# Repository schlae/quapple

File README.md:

# Quapple - A Quadlink Clone
What is a Quadlink? It's an ISA expansion card from the '80s designed to turn your IBM PC (such as a 5150 or 5160) into an Apple \]\[! After booting and running the software, you can switch quickly between PC and Apple mode using Ctrl-Alt-A (for Apple) and Ctrl-Alt-P (for PC).

I'm not selling this board, but the complete design files are available here so you can build it yourself. As an alternative, [a2heaven](http://www.a2heaven.com/webshop/index.php?rt=product/product&product_id=177) sells a kit with the PCB and all the components. (I have not personally built one of these kits.)

All of the components are readily available. In the bill of materials, Mouser part numbers are listed where available. The RAM chips, 27C32 ROM chip, and NE558 may be obtained from a variety of sources in China, but they are not guaranteed to work, so I recommend getting 1 or 2 extras just in case. Note: It has been reported that a Signetics NE558 with a date code of 8825VI, commonly available from China, does not actually work. If you can't find any working 558 chips, try building [my replacement that uses four 555 chips](https://oshpark.com/shared_projects/zHGURt7g).

[Schematic](https://github.com/schlae/quapple/blob/main/Quapple.pdf)

[Bill of Materials](https://github.com/schlae/quapple/blob/main/Quapple.csv)

Please note that the 0.1" header pins are *not* listed on the BOM. They are standard breakaway headers.

The memory chips (4416 and 4164 RAM) are both 150ns types.

[Fab Files](https://github.com/schlae/quapple/blob/main/fab/Quapple-rev1.zip)

## Fabrication Notes
This board is a straight forward 2-layer board. Ideally you should specify selective gold plating (hard gold) for the edge fingers, but this gets very expensive for small orders. ENIG will work but the gold will rub off fairly quickly.

Board dimensions are 13.335" x 4.24" (338.7mm x 107.7mm).

For the soldermask color, pick whatever you want!

## Assembly Notes
I recommend using sockets for the memory chips, CPU, and all the PALS. You'll also need a socket for the joystick/paddle connector. The list of sockets required is as follows:

| Quantity |  Position      | Type              |
|----------|----------------|-------------------|
| 9        | U1-U4, U20-U23, J4 | 16-pin, 0.3" wide |
| 2        | U5, U24        | 18-pin, 0.3" wide |
| 1        | U11            | 24-pin, 0.6" wide |
| 1        | U48            | 40-pin, 0.6" wide |
| 10       | U7, U8, U27, U30, U33, U34, U40, U49, U50, U51 | 20-pin, 0.3" wide |

If you plan to install the card in an IBM 5150 or 5160, you'll plug the floppy drive cable (the one going between the existing controller and the floppy drives in your computer) into the P2 edge connector on the card. **Solder a shrouded header at the J7 position with the keying notch pointing downwards.** Later on, you'll make a short cable to go between the floppy controller card and J7.

If you want to use the card in another system (note: I have not tested this yet!) with a standard IDC header instead of an edge card connector, **solder unshrouded headers at both the J7 and P3 position.** Your existing floppy cable will plug into P3, and you will need to make a short cable that connects J7 and your existing floppy controller card.

J5 and J6 are right-angle 0.1" headers. You can use a single 8-pin strip. Remember to pull pin 2 on both header positions since this is the key for the cable that plugs in. This is also marked on the back of the PC board.

If you are using an NMOS 6502, you can connect the solder jumper on the back of the board right next to the chip. CMOS 6502 chips repurpose this pin and the solder jumper should be left open.

Note for European users: it might be tempting to configure the solder jumpers on the back of the card for PAL timings rather than NTSC, but I have not tested this configuration. The original Quadlink has solder paste covering the jumpers, implying that they never fully tested it. Use it at your own risk.

## Bracket
I've created a CAD model of the original Quadlink bracket. If you have access to sheet metal tools (or even just a chassis nibbler) then you can reproduce it. Once it is in the right shape, bend the top using a press brake or even just a bench vise. The material is 0.035" (0.9mm) steel, brushed and painted black.

[CAD drawing of bracket](https://github.com/schlae/quapple/blob/main/mech/bracket.dxf)

## Programmable Devices
There are 11 programmable devices on the Quapple. One of them is a 27C32 EPROM which contains the character set for the text mode. I didn't have much luck using the Minipro TL866 device to program my Intel 2732 devices, so you might have to try a few to find one that works. You might also try using a flash device (28C32?) instead, but I have not tested this myself.

[EPROM binary](https://github.com/schlae/quapple/blob/main/eprom/U11QL100.bin)

The remaining programmable devices are all PALs. You can use an ATF16V8 (speed grade is unimportant here), which happens to be supported by the Minipro TL866.

[PAL files](https://github.com/schlae/quapple/tree/main/pals)

Use the JEDEC files (.jed) with the following Minipro command line under Linux:

`minipro -p "ATF16V8B" -w [file.jed] -P`

The full, commented, PAL source code is provided for educational purposes. If you want to modify them, you can use WinCUPL to build them.

I recommend marking the PALs with colored dots, labels, or permanent marker so you don't mix them up and put them in the wrong sockets.

PAL functions are as follows:

| Position   |   Function    |
|------------|---------------|
| U8         | Video address decoding (simple) |
| U27        | Video address decoding (complex). Video sync. |
| U7         | Clock generation |
| U30        | Soft switches |
| U33        | Color attribute generation |
| U34        | ISA bus address decoder |
| U40        | Disk controller |
| U49        | 6502 state machine |
| U50        | More soft switches |
| U51        | RAM/ROM mapping, CAS control, RESET inverter |

## Cable assemblies
You will also need to build several cable assemblies to connect the Quapple to your PC.

### Floppy drive cable
For use with an IBM 5150 or 5160, make a short, 6" (15cm) IDC ribbon cable, 34 pin, with a 0.1" female header at one end and a 34-pin female edge connector at the other end.

For any other computer, just crimp a 34-pin 0.1" female header at both ends. Be sure not to get pin 1 mixed up--it is very easy to do!

### Video loopback cable
To use the same monitor for both Apple and PC mode, you'll need a short cable to go between the Quapple and your regular video card (MDA or CGA). This is just a short cable with a male DE-9 connector at both ends, wired straight through (pin 1 to pin 1, etc).

The stock cable is 12" (30.5cm) long and uses a TE Connectivity/AMP 745032-1 connector, along with a cord guard, 207753-1, at both ends. The contact part number is 1-66506-0. The cable is 0.24" (6mm) diameter with eight conductors (the drain wire is connected to pin 1).

### PC speaker jumper
To hear Apple sound through the PC speaker, make a short 2-wire cable (maybe 2-3" long, depending on your computer). This goes from the motherboard to the Quapple.

The cable should be wired as follows:

* Pin 1 connects to pin 1 (black wire)
* Pin 2 is a key (plastic peg inserted in the opening) at both ends
* Pin 3 is not used
* Pin 4 to pin 4 (yellow wire)

## Installation
You'll want to install the card in the second-to-last slot (5150) or third-from-last slot (5160). This is because the floppy controller should be in between the Quapple and the power supply, just to make cable routing easier.

Before you start, plug the short floppy jumper cable into J7 on the Quapple. Also plug the 4-pin PC speaker jumper cable into header J6.

Remove the floppy controller and disconnect the drive cable from it. Plug the drive cable into the Quapple connector P2 (or P3, if the cable has a 0.1" socket at the end). Unplug the PC speaker from the motherboard.

Then plug the Quapple into the PC slot, managing the floppy cable as needed. The 4-pin jumper should plug into the motherboard's PC speaker header, and the PC speaker cable should plug into J5.

Then plug the short floppy jumper cable into the header on the floppy controller, and plug the floppy controller back into an adjacent slot. Since the card is shorter, it's much easier to use the slot that is closer to the power supply.

Finally, connect the DE-9 jumper cable between the video card and the *lower* connector on the Quapple. This step is optional since you can use the card with a dual monitor configuration, or even with the composite video output jack.

## Software
You can find the software at the link below, along with the manual of the original Quadlink. There are *three* disk images you will need: the Quadlink System Master, the Quadlink Filer, and DOS (I used PC DOS 1.10, but feel free to experiment). The Quadlink System Master disk has an executable, QUADLINK.EXE, which should be copied to the DOS disk.

The Filer disk can be written using a flux imaging tool, or possibly with an Apple II running ADTPro.

[Software download](https://www.diskman.com/presents/trackstar/software.htm)

A note about compatibility: I have only tested the card in an IBM 5150. It's supposed to work in a 5160 as well. Based on looking at the design, I see no reason why it wouldn't work in a faster machine, but there may be CPU-dependent hardware loops in the Quadlink executable that would prevent it from working.

Once you have the disks, insert the DOS disk and turn on the computer. After it boots, run QUADLINK.EXE and follow the prompts. When you insert the Filer disk, the software copies the entire Applesoft ROM from the disk into a special 16K memory on the card and write-protects it. Hit a key to get back to DOS, and then press CTRL-ALT-A. If you see the Quadlink banner, hit CTRL-ALT-DEL to boot the Apple.

## Troubleshooting
This can be a tricky card to troubleshoot. The QUADLINK.EXE doesn't really provide good error diagnostics, but if you can get it to access the Filer disk, then you know that the 6502 is running code and trying to copy data from the disk.

Someday, when I get a chance, I'll look into writing a diagnostic program to help with the process...

## License
This work is licensed under a Creative Commons Attribution-ShareAlike 4.0
International License. See [https://creativecommons.org/licenses/by-sa/4.0/](https://creativecommons.org/licenses/by-sa/4.0/).

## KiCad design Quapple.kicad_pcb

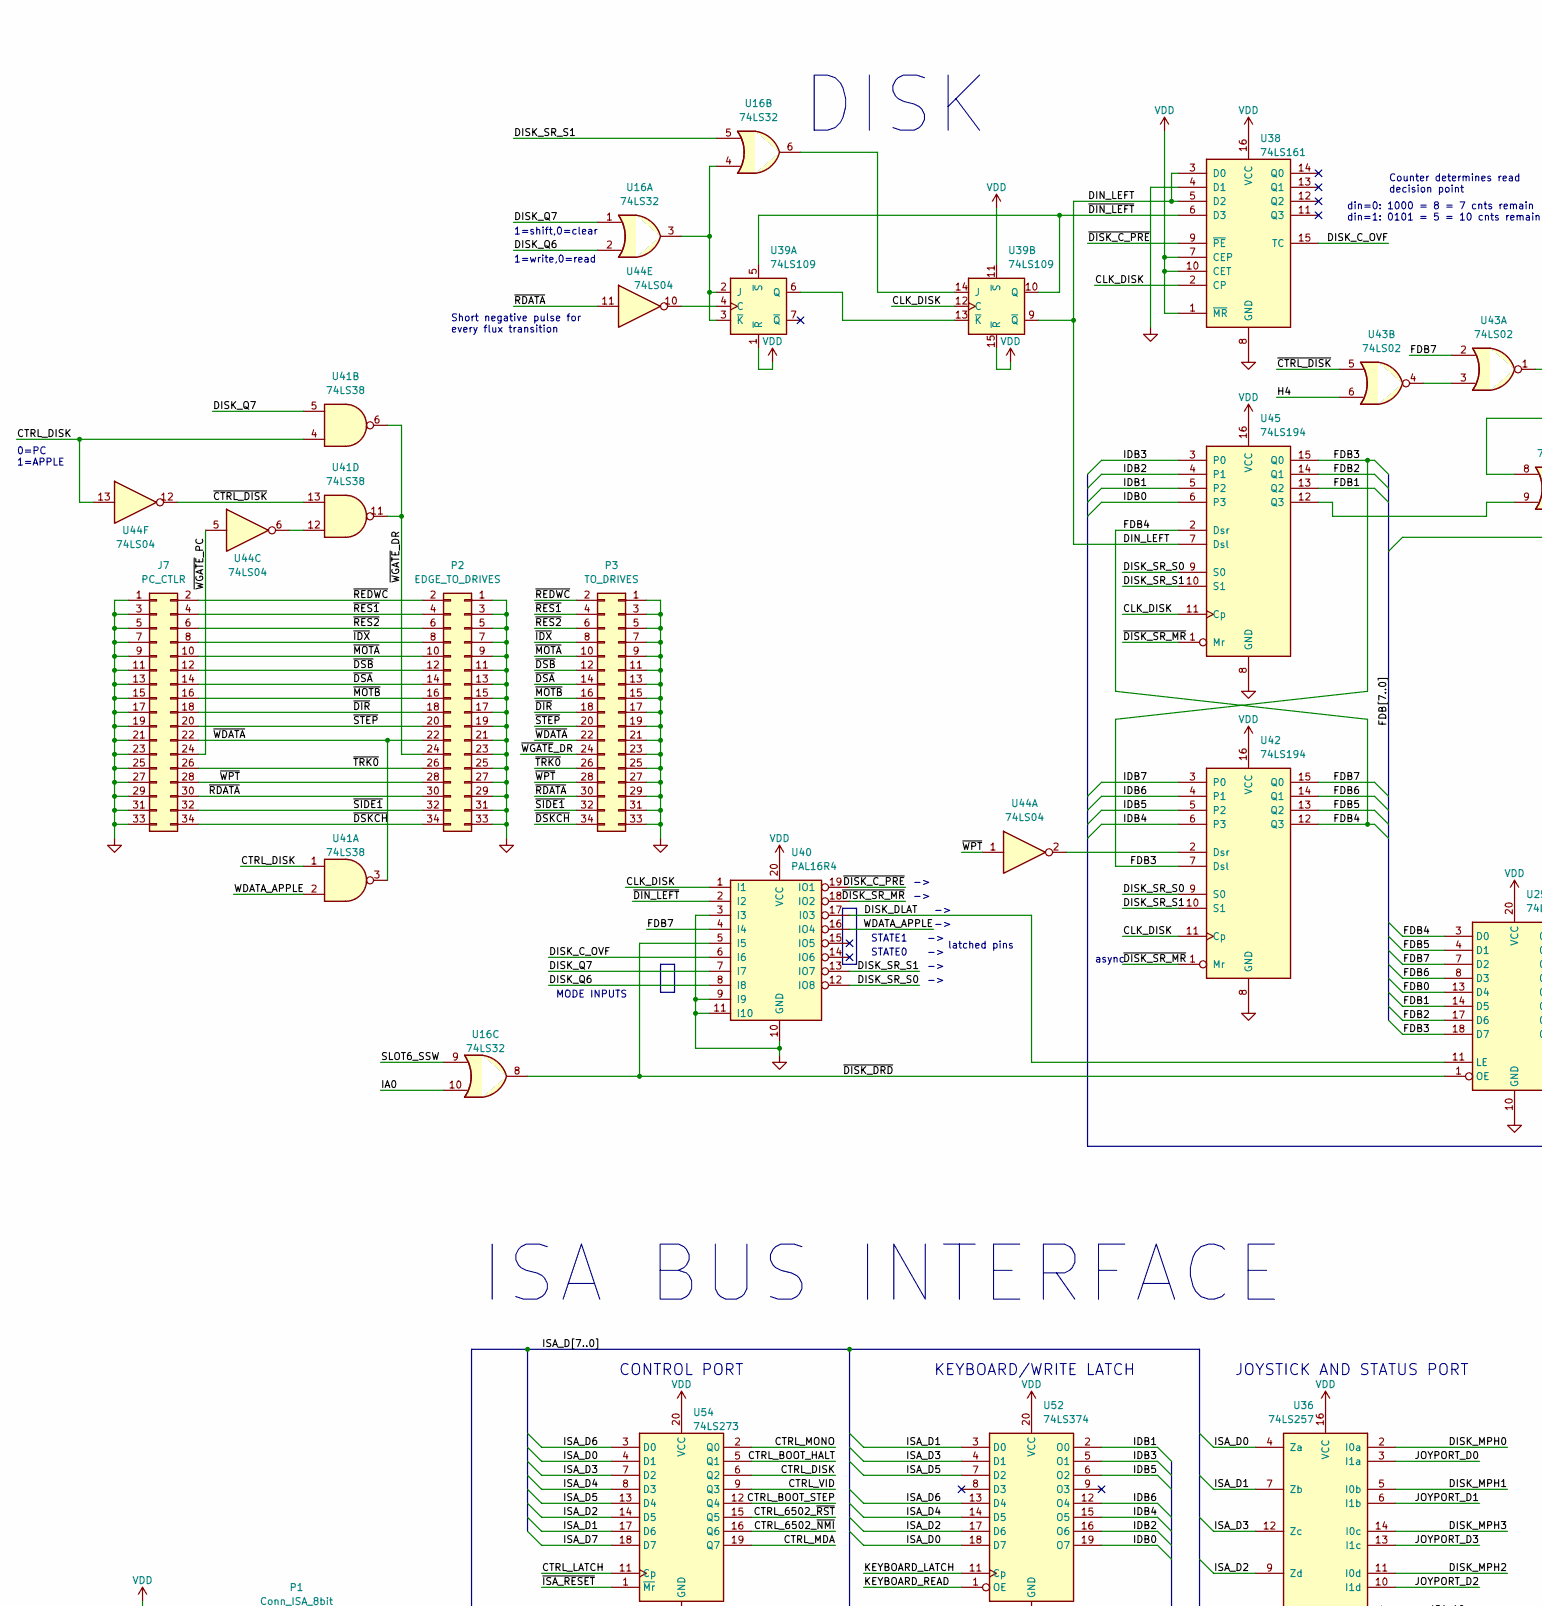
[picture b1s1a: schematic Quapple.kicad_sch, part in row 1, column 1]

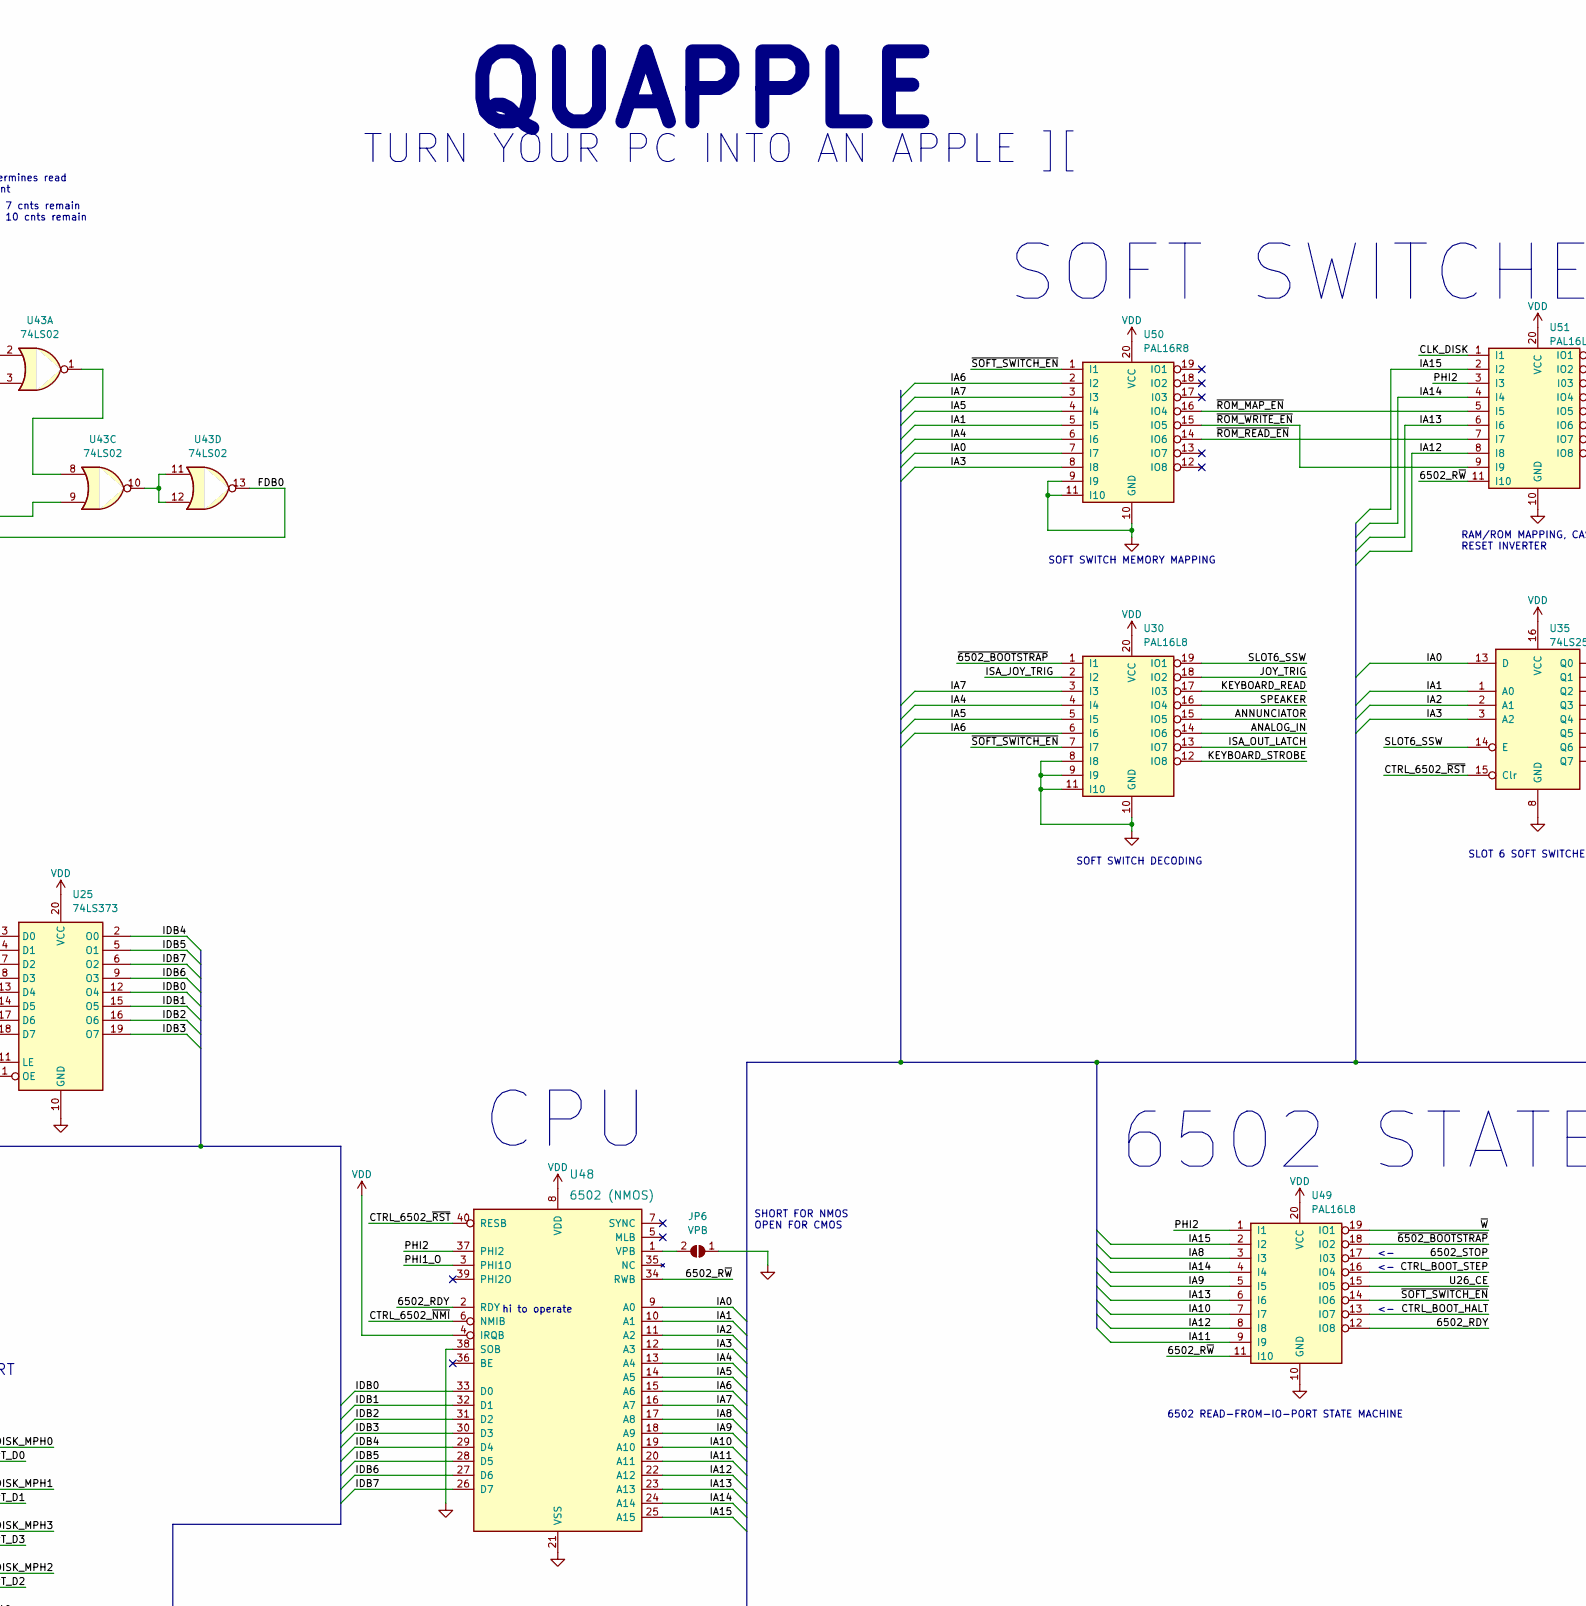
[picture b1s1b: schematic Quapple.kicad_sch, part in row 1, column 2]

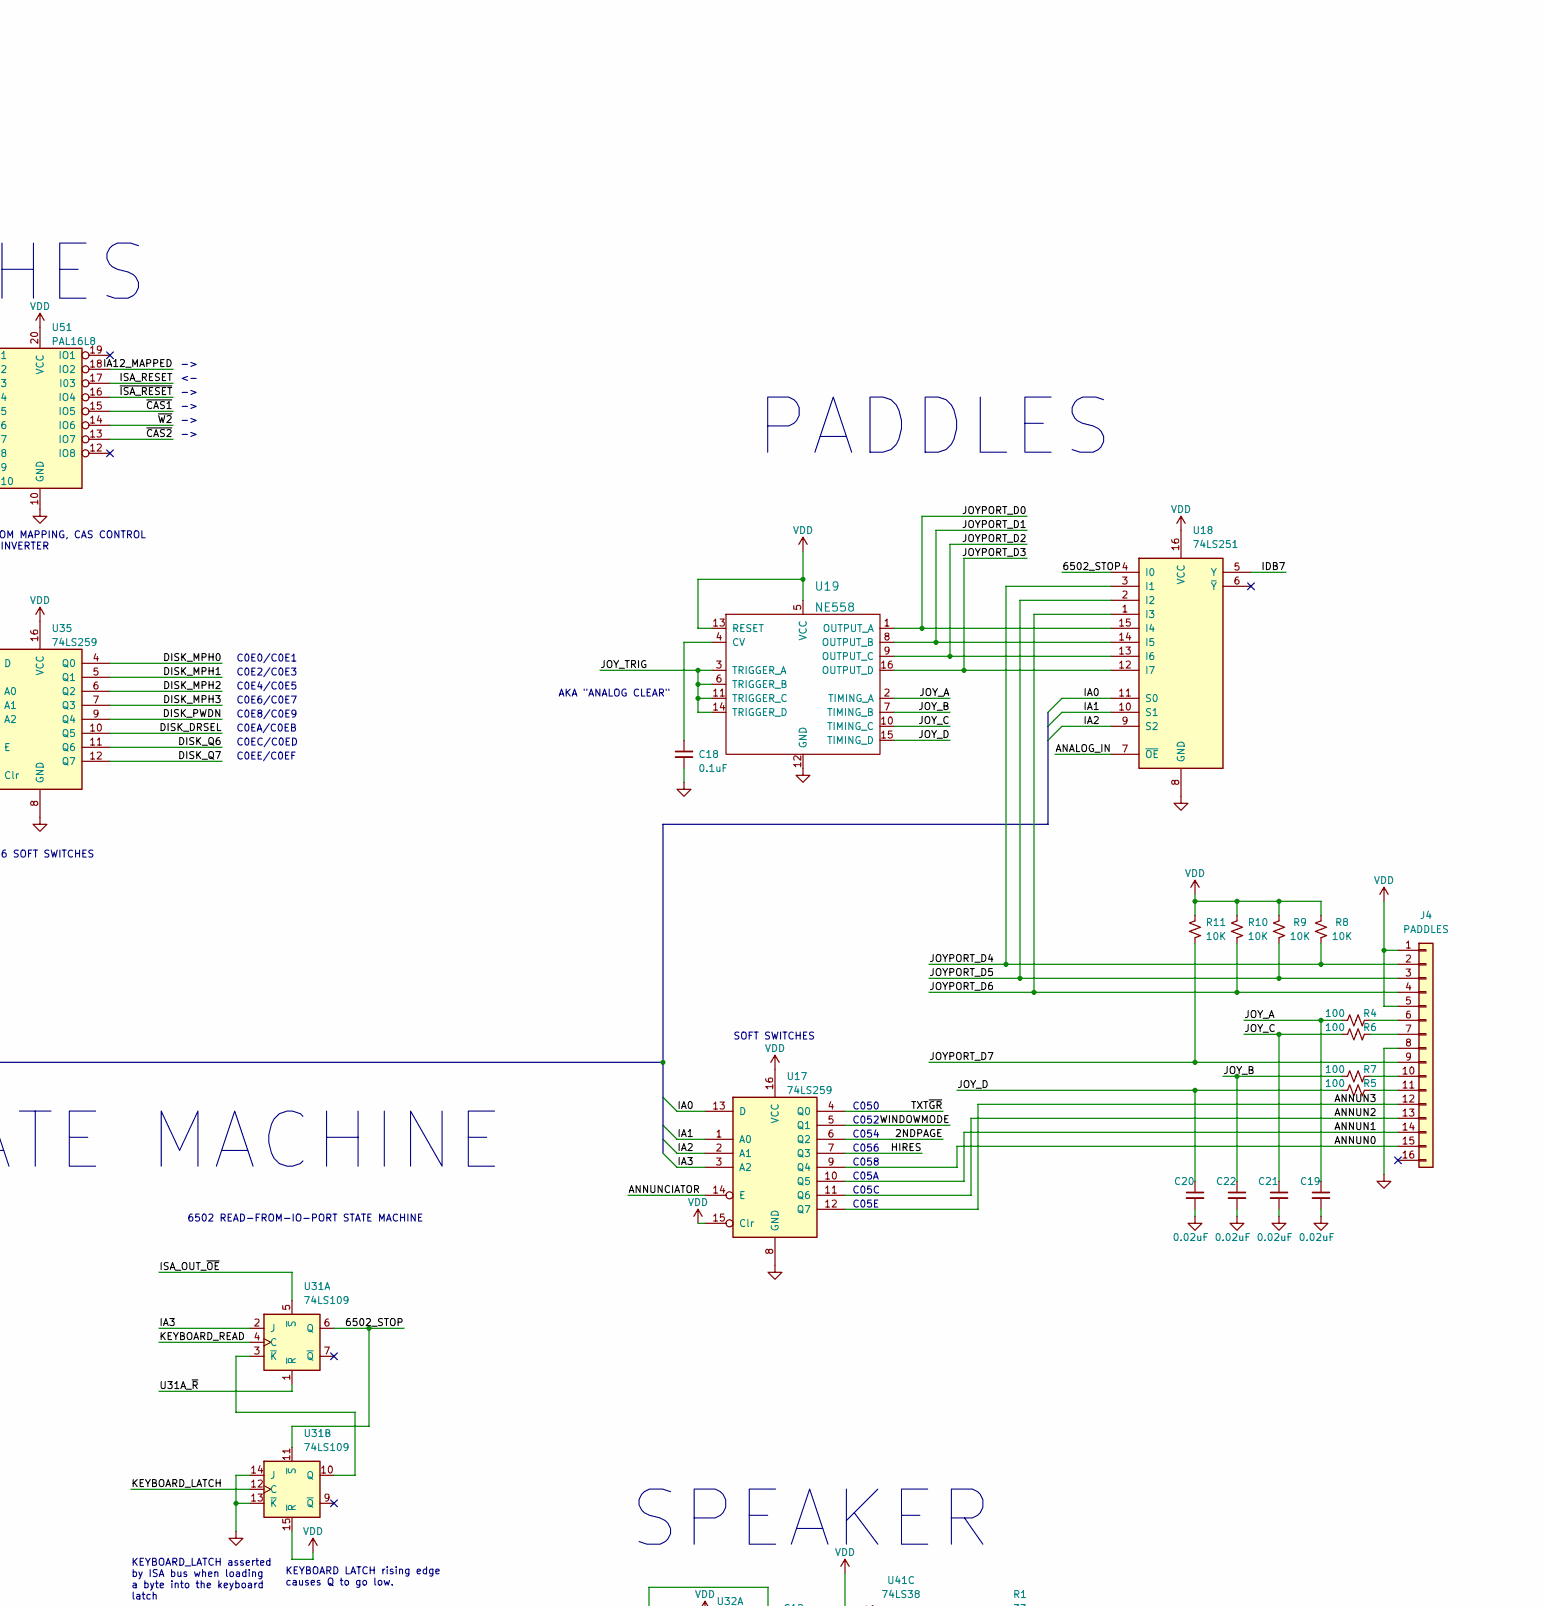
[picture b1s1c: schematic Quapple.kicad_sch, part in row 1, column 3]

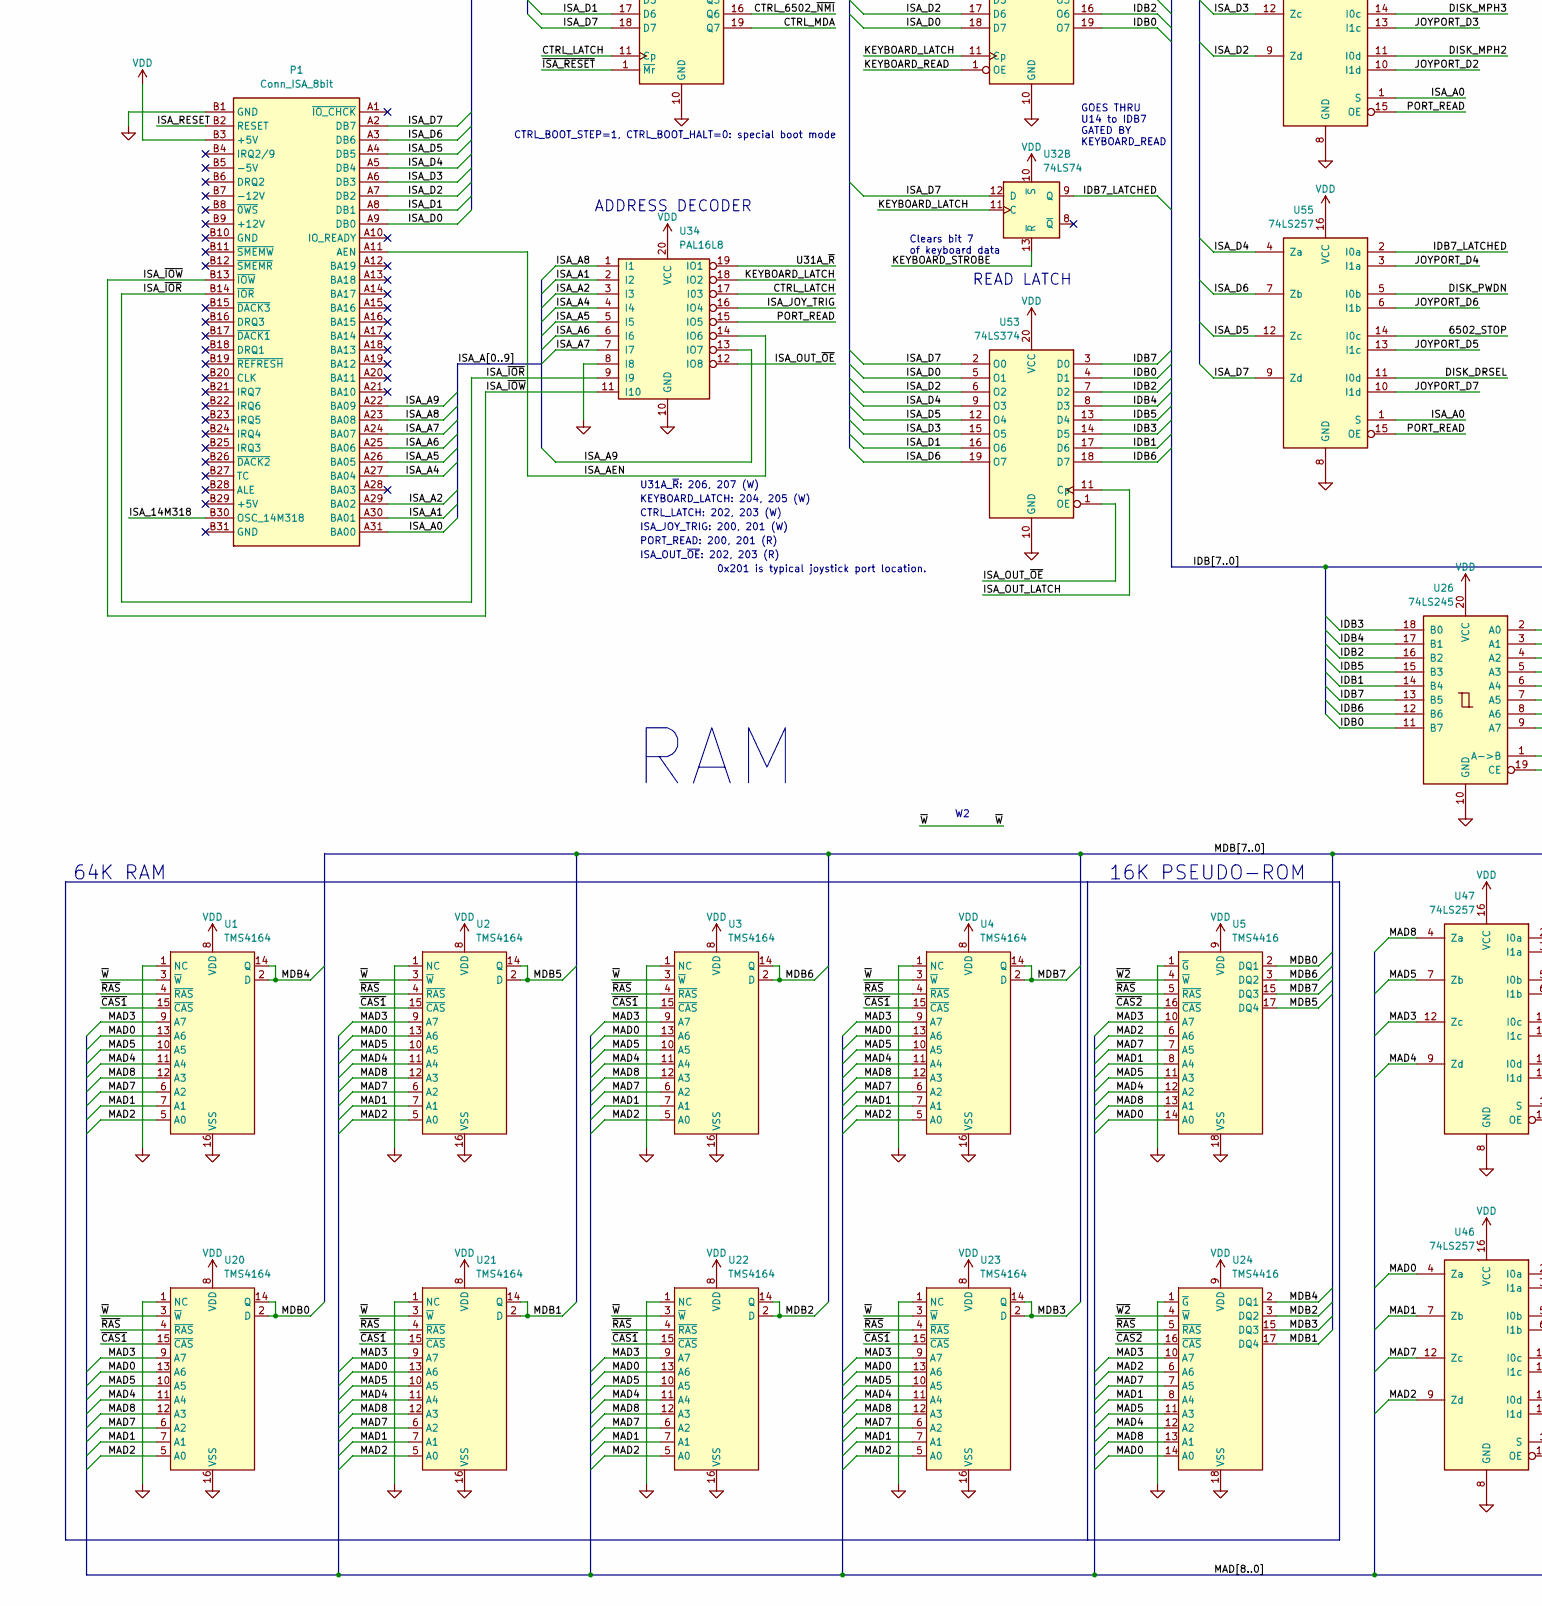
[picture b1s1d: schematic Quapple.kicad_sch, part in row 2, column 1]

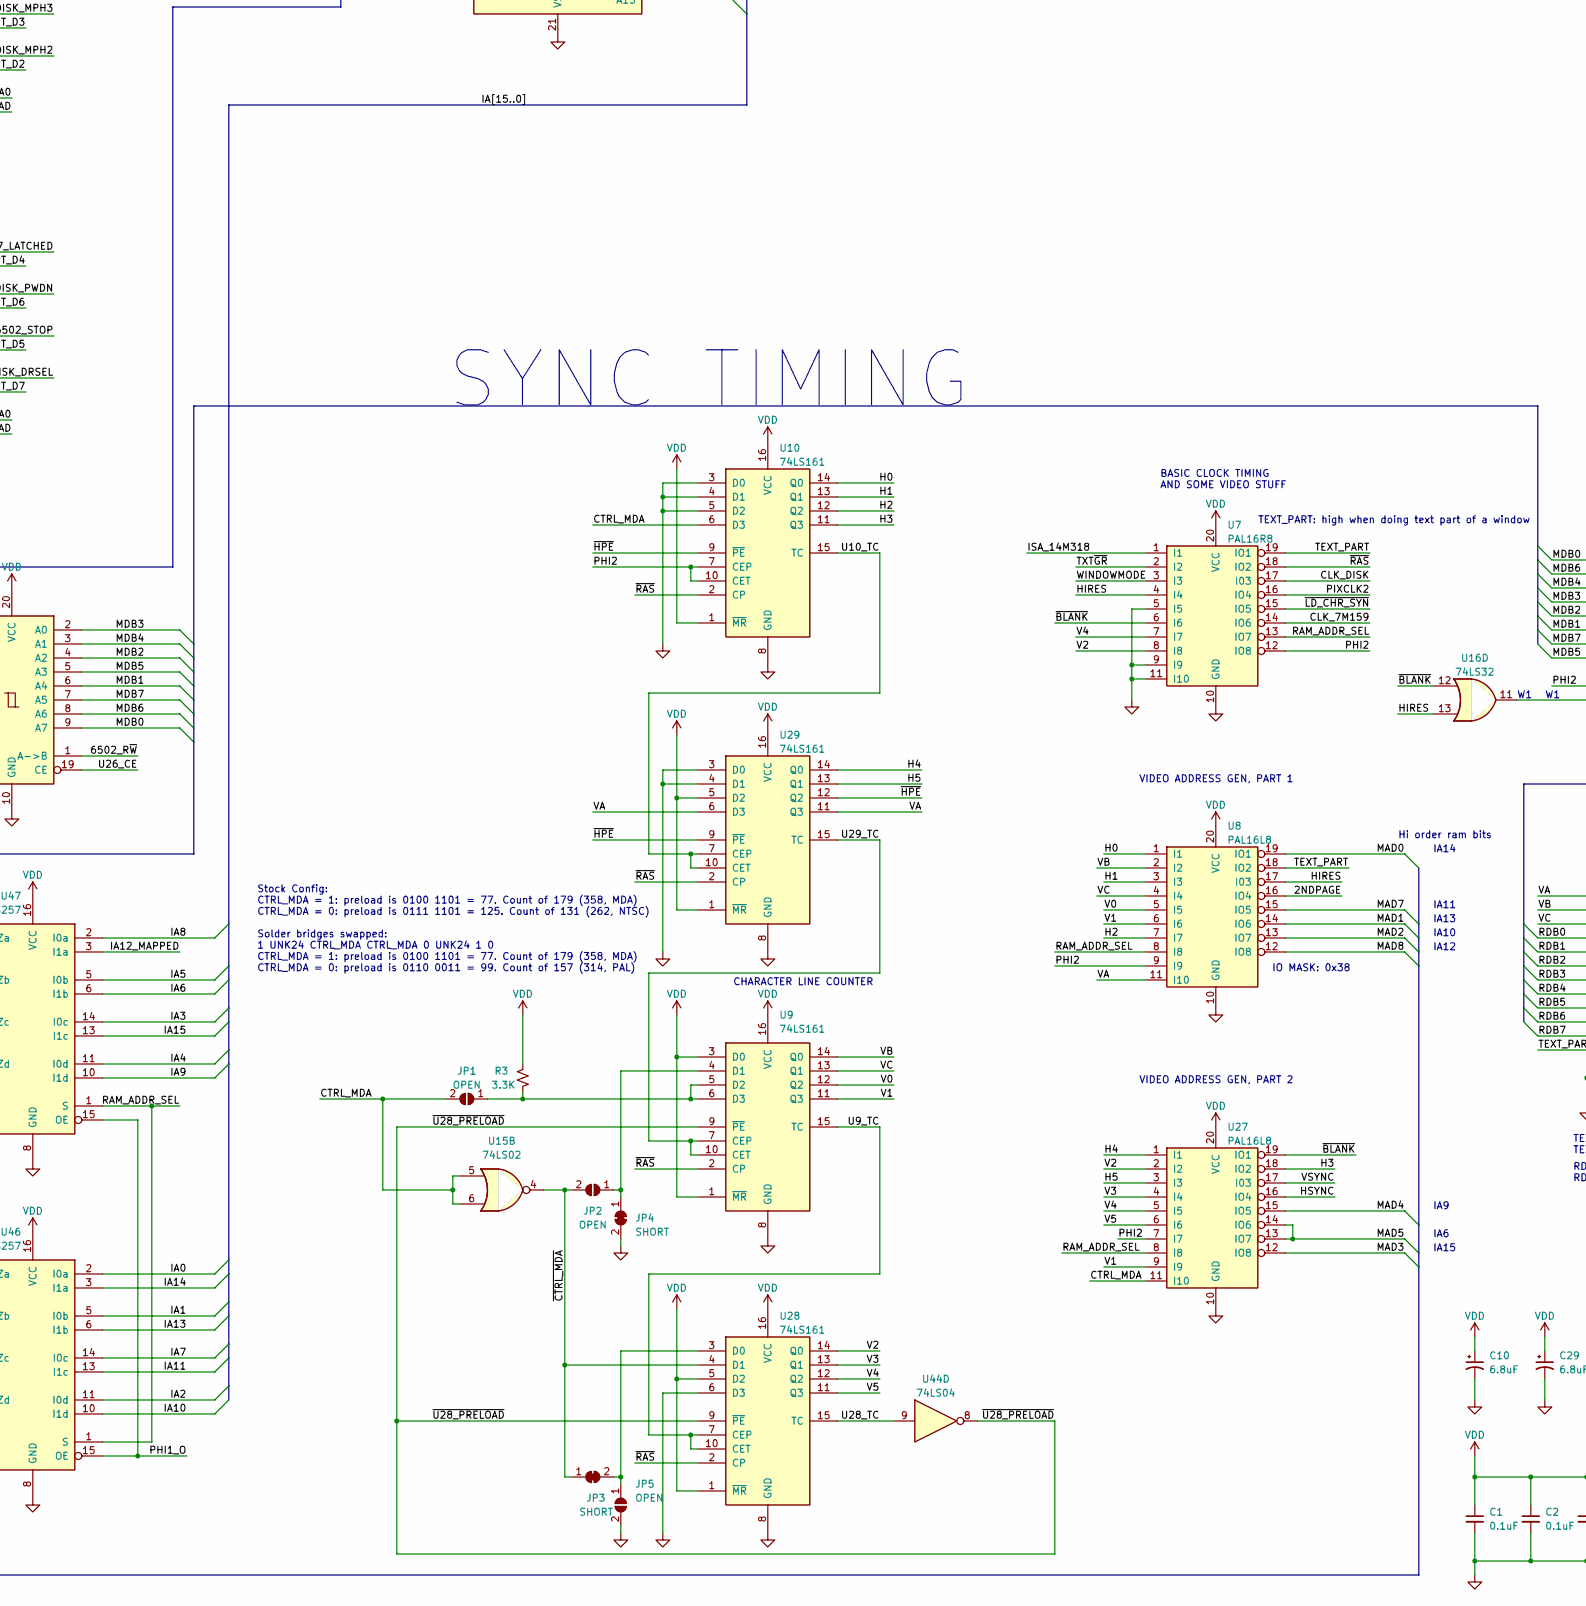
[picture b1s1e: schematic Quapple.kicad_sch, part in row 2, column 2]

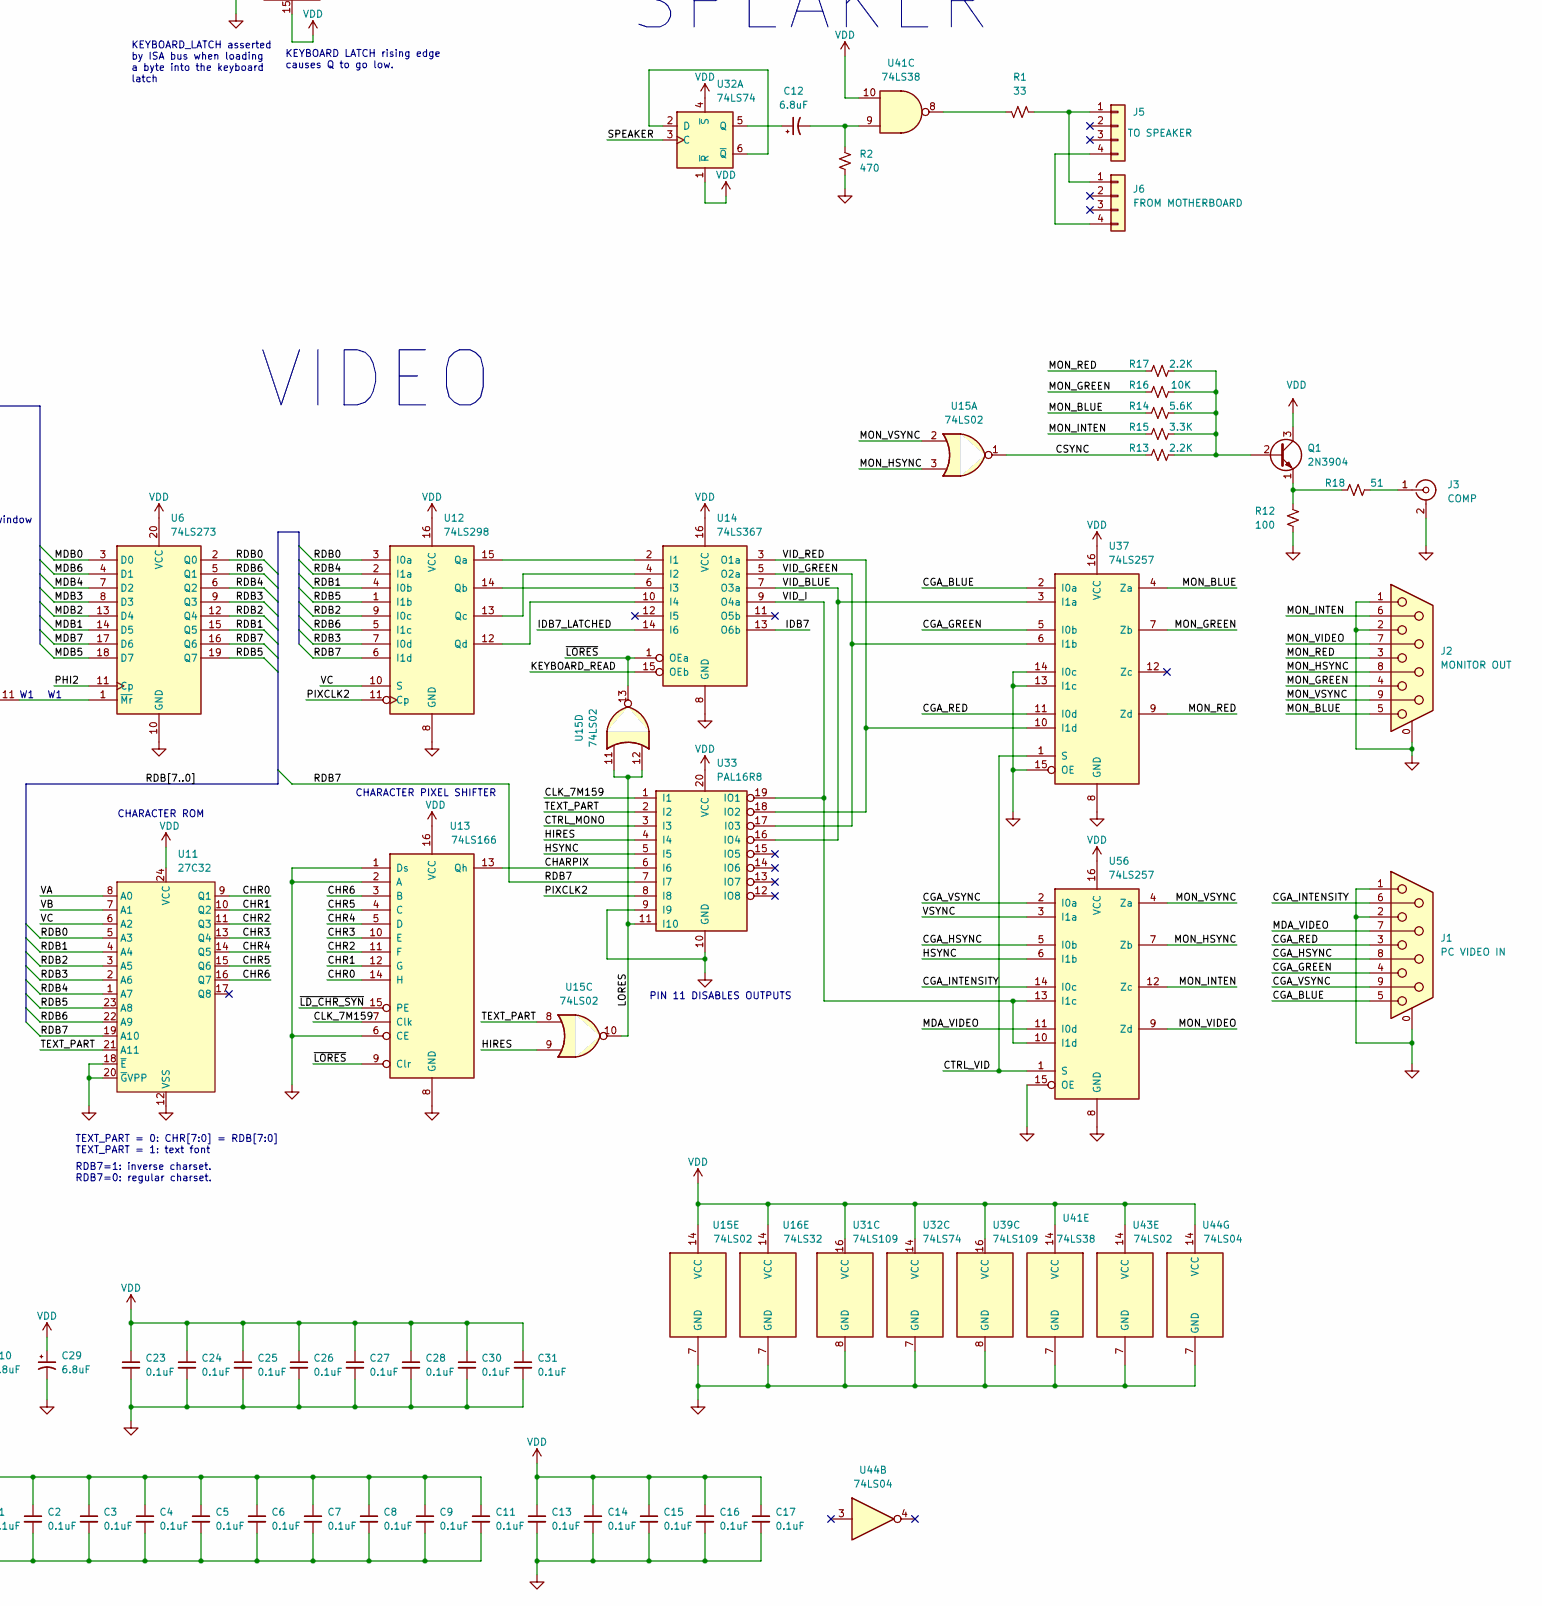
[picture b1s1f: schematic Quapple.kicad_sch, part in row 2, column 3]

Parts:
C1, C2, C3, C4, C5, C6, C7, C8, C11, C13, C14, C15, C16, C17, C18, C23, C24, C25, C26, C27, C28, C30, C31: 0.1uF; CAP300; Mouser 594-K104K15X7RF5TH5
C9: 0.1uF; CAP300_THIN; Mouser 594-K104K15X7RF5TH5
C10, C12, C29: 6.8uF; CAP300_P; Mouser 667-ECA-1HM100I
C19, C20, C21, C22: 0.02uF; CAP300_THIN; Mouser 81-RDE7U3A203JUE1H3A
J1: PC VIDEO IN; DB9; Mouser 523-G17C0900132EU
J2: MONITOR OUT; DB9; Mouser 523-G17C0900132EU
J3: COMP; RCA_JACK; Mouser 502-3517PCX
J4: PADDLES; DIP16_ALT; Mouser 517-4816-3004-CP
J5: TO SPEAKER; HDR100-4; Mouser 538-22-28-6043
J6: FROM MOTHERBOARD; HDR100-4; Mouser 538-22-28-6043
J7: PC_CTLR; HDR100-34; Mouser 571-5103308-7
JP1, JP2: OPEN; BRIDGE1_O
JP3: SHORT; BRIDGE3_S
JP4: SHORT; BRIDGE2_S
JP5: OPEN; BRIDGE4
JP6: VPB; BRIDGE1_O
P1: Conn_ISA_8bit; EDGE_ISA_8BIT
P2: EDGE_TO_DRIVES; EDGE_34
P3: TO_DRIVES; HDR100-34; Mouser 571-5103308-7
Q1: 2N3904; TO92; Mouser 610-2N3904
R1: 33; RES500; Mouser 603-CFR-25JR-5233R
R2: 470; RES500; Mouser 603-CFR-25JR-52470R
R3, R15: 3.3K; RES500; Mouser 603-CFR-25JR-523K3
R4, R5, R6, R7, R12: 100; RES500; Mouser 603-CFR-25JR-52100R
R8, R9, R10, R11: 10K; RES420; Mouser 603-CFR-25JR-5210K
R13, R17: 2.2K; RES500; Mouser 603-CFR-25JR-522K2
R14: 5.6K; RES500; Mouser 603-CFR-25JR-525K6
R16: 10K; RES500; Mouser 603-CFR-25JR-5210K
R18: 51; RES420; Mouser 603-CFR-25JR-5251R
U1, U2, U3, U4, U20, U21, U22, U23: TMS4164; DIP16
U5, U24: TMS4416; DIP18
U6, U54: 74LS273; DIP20; Mouser 595-SN74LS273N
U7, U33, U50: PAL16R8; DIP20; Mouser 556-AF16V8CZ15PU
U8, U27, U30, U34, U49, U51: PAL16L8; DIP20; Mouser 556-AF16V8CZ15PU
U9, U10, U28, U29, U38: 74LS161; DIP16; Mouser 595-SN74LS161AN
U11: 27C32; DIP24
U12: 74LS298; DIP16; Mouser 595-SN74LS298N
U13: 74LS166; DIP16; Mouser 595-SN74LS166AN
U14: 74LS367; DIP16; Mouser 595-SN74LS367AN
U15, U43: 74LS02; DIP14; Mouser 595-SN74LS02N
U16: 74LS32; DIP14; Mouser 595-SN74LS32N
U17, U35: 74LS259; DIP16; Mouser 595-SN74LS259BN
U18: 74LS251; DIP16; Mouser 595-SN74LS251N
U19: NE558; DIP16
U25: 74LS373; DIP20; Mouser 595-SN74LS373N
U26: 74LS245; DIP20; Mouser 595-SN74LS245N
U31, U39: 74LS109; DIP16; Mouser 595-SN74LS109AN
U32: 74LS74; DIP14; Mouser 595-SN74LS74AN
U36, U37, U46, U47, U55, U56: 74LS257; DIP16; Mouser 595-SN74LS257BN
U40: PAL16R4; DIP20; Mouser 556-AF16V8CZ15PU
U41: 74LS38; DIP14; Mouser 595-SN74LS38N
U42, U45: 74LS194; DIP16; Mouser 595-SN74LS194AN
U44: 74LS04; DIP14; Mouser 595-SN74LS04N
U48: 6502 (NMOS); DIP40; Mouser 955-W65C02S6TPG-14
U52, U53: 74LS374; DIP20; Mouser 595-SN74LS374N

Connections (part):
/2NDPAGE: U8.16 (IO4), U17.6 (Q2)
/6502_RDY: U48.2 (RDY), U49.12 (IO8)
/6502_R~W: U26.1 (A->B), U48.34 (RWB), U49.11 (I10), U51.11 (I10)
/6502_STOP: U18.4 (I0), U31.6 (Q), U31.11 (~S), U49.17 (I03), U55.14 (I0c)
/ANALOG_IN: U18.7 (~OE), U30.14 (IO6)
/ANNUN0: J4.15, U17.9 (Q4)
/ANNUN1: J4.14, U17.10 (Q5)
/ANNUN2: J4.13, U17.11 (Q6)
/ANNUN3: J4.12, U17.12 (Q7)
/ANNUNCIATOR: U17.14 (E), U30.15 (IO5)
/CGA_BLUE: J1.5, U37.2 (I0a)
/CGA_GREEN: J1.4, U37.5 (I0b)
/CGA_HSYNC: J1.8, U56.5 (I0b)
/CGA_INTENSITY: J1.6, U56.14 (I0c)
/CGA_RED: J1.3, U37.11 (I0d)
/CGA_VSYNC: J1.9, U56.2 (I0a)
/CHARPIX: U13.13 (Qh), U33.6 (I6)
/CHR0: U11.9 (Q1), U13.14 (H)
/CHR1: U11.10 (Q2), U13.12 (G)
/CHR2: U11.11 (Q3), U13.11 (F)
/CHR3: U11.13 (Q4), U13.10 (E)
/CHR4: U11.14 (Q5), U13.5 (D)
/CHR5: U11.15 (Q6), U13.4 (C)
/CHR6: U11.16 (Q7), U13.3 (B)
/CLK_7M159: U7.14 (IO6), U13.7 (Clk), U33.1 (I1)
/CLK_DISK: U7.17 (I03), U38.2 (CP), U39.12 (C), U40.1 (I1), U42.11 (Cp), U45.11 (Cp), U51.1 (I1)
/CSYNC: R13.1, U15.1
/CTRL_6502_~NMI: U48.6 (NMIB), U54.16 (Q6)
/CTRL_6502_~RST: U35.15 (Clr), U48.40 (RESB), U54.15 (Q5)
/CTRL_BOOT_HALT: U49.13 (IO7), U54.5 (Q1)
/CTRL_BOOT_STEP: U49.16 (IO4), U54.12 (Q4)
/CTRL_DISK: U41.1, U41.4, U44.13, U54.6 (Q2)
/CTRL_LATCH: U34.17 (I03), U54.11 (Cp)
/CTRL_MDA: JP1.2 (B), U10.6 (D3), U15.5, U15.6, U27.11 (I10), U54.19 (Q7)
/CTRL_MONO: U33.3 (I3), U54.2 (Q0)
/CTRL_VID: U37.1 (S), U54.9 (Q3), U56.1 (S)
/DIN_LEFT: U38.3 (D0), U38.5 (D2), U39.9 (~Q), U45.7 (Dsl)
/DISK_C_OVF: U38.15 (TC), U40.6 (I6)
/DISK_DLAT: U25.11 (LE), U40.17 (I03)
/DISK_DRSEL: U35.10 (Q5), U55.11 (I0d)
/DISK_MPH0: U35.4 (Q0), U36.2 (I0a)
/DISK_MPH1: U35.5 (Q1), U36.5 (I0b)
/DISK_MPH2: U35.6 (Q2), U36.11 (I0d)
/DISK_MPH3: U35.7 (Q3), U36.14 (I0c)
/DISK_PWDN: U35.9 (Q4), U55.5 (I0b)
/DISK_Q6: U16.2, U35.11 (Q6), U40.8 (I8)
/DISK_Q7: U16.1, U35.12 (Q7), U40.7 (I7), U41.5
/DISK_SR_S0: U40.12 (IO8), U42.9 (S0), U45.9 (S0)
/DISK_SR_S1: U16.5, U40.13 (IO7), U42.10 (S1), U45.10 (S1)
/FDB0: U25.13 (D4), U43.13
/FDB1: U25.14 (D5), U45.13 (Q2)
/FDB2: U25.17 (D6), U45.14 (Q1)
/FDB3: U25.18 (D7), U42.7 (Dsl), U45.15 (Q0)
/FDB4: U25.3 (D0), U42.12 (Q3), U45.2 (Dsr)
/FDB5: U25.4 (D1), U42.13 (Q2)
/FDB6: U25.8 (D3), U42.14 (Q1)
/FDB7: U25.7 (D2), U40.4 (I4), U42.15 (Q0), U43.2
/H0: U8.1 (I1), U10.14 (Q0)
/H1: U8.3 (I3), U10.13 (Q1)
/H2: U8.7 (I7), U10.12 (Q2)
/H3: U10.11 (Q3), U27.18 (IO2)
/H4: U27.1 (I1), U29.14 (Q0), U43.6
/H5: U27.3 (I3), U29.13 (Q1)
/HIRES: U7.4 (I4), U8.17 (I03), U15.9, U16.13, U17.7 (Q3), U33.4 (I4)
/HSYNC: U27.16 (IO4), U33.5 (I5), U56.6 (I1b)
/IA0: U16.10, U17.13 (D), U18.11 (S0), U35.13 (D), U46.2 (I0a), U48.9 (A0), U50.7 (I7)
/IA1: U17.1 (A0), U18.10 (S1), U35.1 (A0), U46.5 (I0b), U48.10 (A1), U50.5 (I5)
/IA2: U17.2 (A1), U18.9 (S2), U35.2 (A1), U46.11 (I0d), U48.11 (A2)
/IA3: U17.3 (A2), U31.2 (J), U35.3 (A2), U47.14 (I0c), U48.12 (A3), U50.8 (I8)
/IA4: U30.4 (I4), U47.11 (I0d), U48.13 (A4), U50.6 (I6)
/IA5: U30.5 (I5), U47.5 (I0b), U48.14 (A5), U50.4 (I4)
/IA6: U30.6 (I6), U47.6 (I1b), U48.15 (A6), U50.2 (I2)
/IA7: U30.3 (I3), U46.14 (I0c), U48.16 (A7), U50.3 (I3)
/IA8: U47.2 (I0a), U48.17 (A8), U49.3 (I3)
/IA9: U47.10 (I1d), U48.18 (A9), U49.5 (I5)
/IA10: U46.10 (I1d), U48.19 (A10), U49.7 (I7)
/IA11: U46.13 (I1c), U48.20 (A11), U49.9 (I9)
/IA12: U48.22 (A12), U49.8 (I8), U51.8 (I8)
/IA12_MAPPED: U47.3 (I1a), U51.18 (IO2)
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
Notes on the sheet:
16K PSEUDO-ROM
C052
async
CTRL_LATCH: 202, 203 (W)
6502 STATE MACHINE
SPEAKER
CPU
CONTROL PORT
RAM
AKA "ANALOG CLEAR"
TURN YOUR PC INTO AN APPLE ][
Counter determines read decision point
SYNC TIMING
C0E4/C0E5
Hi order ram bits
SLOT 6 SOFT SWITCHES
C056
ISA_JOY_TRIG: 200, 201 (W)
latched pins
CHARACTER LINE COUNTER
IA12
C0E2/C0E3
CHARACTER PIXEL SHIFTER
C0EE/C0EF
KEYBOARD_LATCH: 204, 205 (W)
IA9
C054
READ LATCH
VIDEO
RAM/ROM MAPPING, CAS CONTROL RESET INVERTER
Clears bit 7 of keyboard data
STATE0
IA15
BASIC CLOCK TIMING AND SOME VIDEO STUFF
C05E
6502 READ-FROM-IO-PORT STATE MACHINE
C0E0/C0E1
RDB7=1: inverse charset. RDB7=0: regular charset.
C0E8/C0E9
C050

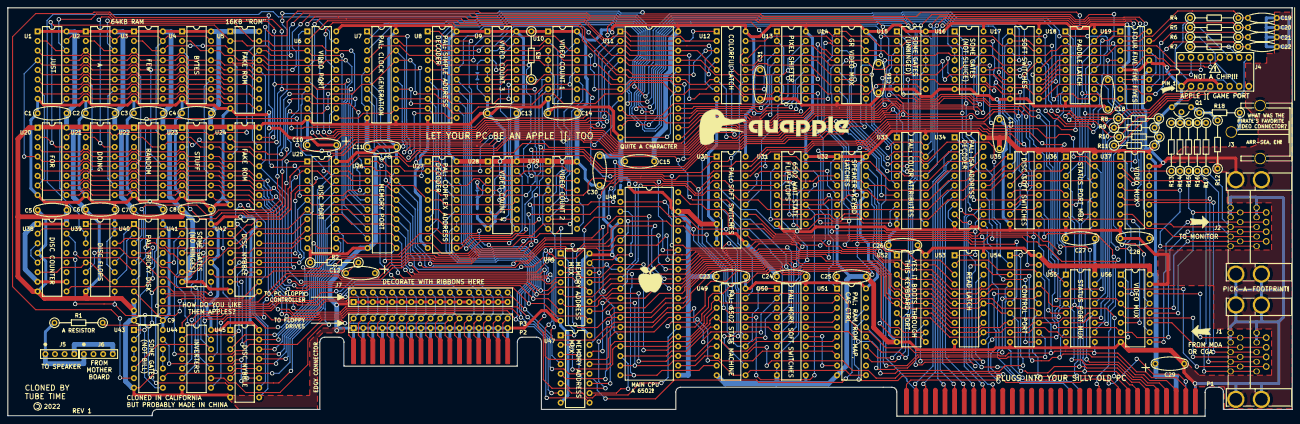
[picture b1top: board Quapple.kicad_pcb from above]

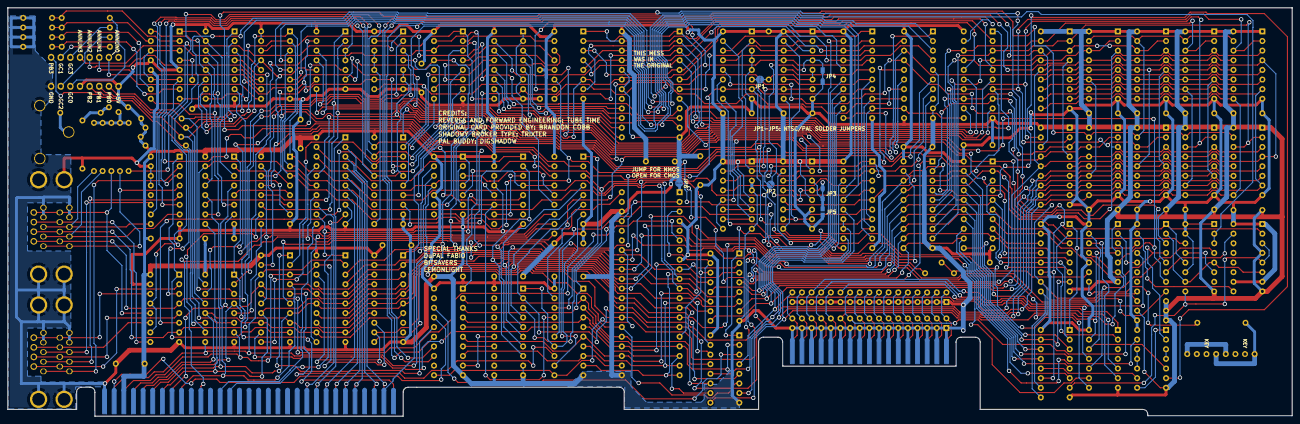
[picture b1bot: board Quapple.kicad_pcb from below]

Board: 2 copper layers, 338.7 x 107.7 mm, 122 parts (6 on the bottom side), 272 nets.

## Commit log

2022-05-13 initial empty commit
2022-05-13 rev 1 fab files
2022-05-16 update bracket, video cable description
2022-07-15 Fix composite mode resistor
2022-08-29 Update software link
2022-09-29 Update readme with a2heaven link

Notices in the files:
Quapple.kicad_pcb:
(C) 2022 Tube Time
http://creativecommons.org/licenses/by-sa/4.0
This work is licensed under the Creative Commons
